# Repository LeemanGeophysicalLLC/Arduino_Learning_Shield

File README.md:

# Arduino_Learning_Shield
Shield to teach the basics of the Arduino platform.

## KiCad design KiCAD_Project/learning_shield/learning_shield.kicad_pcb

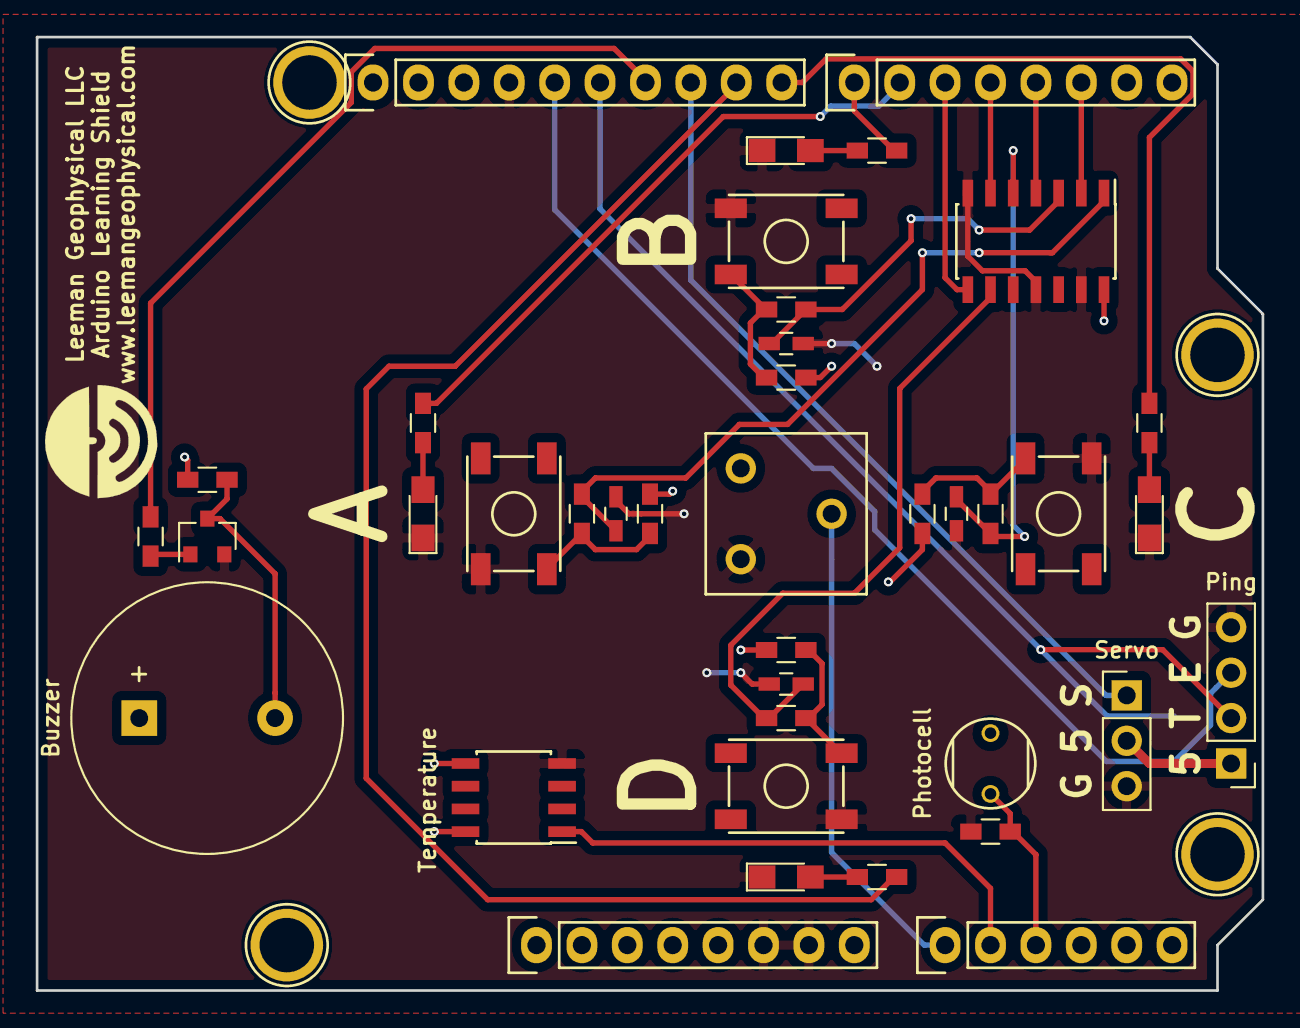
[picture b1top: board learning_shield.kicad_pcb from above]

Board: 2 copper layers, 68.6 x 53.3 mm, 43 parts (0 on the bottom side), 31 nets.

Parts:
BZ1: Buzzer; Buzzer_15x7.5RM7.6
C1, C2, C3, C4: C; C_0603_HandSoldering
D1, D2, D3, D4: LED A; LED_0805_HandSoldering
J1: Ping Sensor; Pin_Header_Straight_1x04_Pitch2.54mm
J2: Servo; Pin_Header_Straight_1x03_Pitch2.54mm
P1: Power; Socket_Strip_Arduino_1x08
P2: Analog; Socket_Strip_Arduino_1x06
P3: Digital; Socket_Strip_Arduino_1x10
P4: Digital; Socket_Strip_Arduino_1x08
P5, P6, P7, P8: CONN_01X01; Arduino_1pin
Q1: MMBT3904; SOT-23
R1, R2, R3, R4, R5, R6, R7, R8, R10: 10k; R_0603_HandSoldering
R9: R_PHOTO; photoresistor
R11, R12, R13, R14: 510; R_0603_HandSoldering
R15, R16: 1k; R_0603_HandSoldering
RV1: R_POT; ebay_potentiometer
SW1: Switch A; ebay_button
SW2: Switch B; ebay_button
SW3: Switch C; ebay_button
SW4: Switch D; ebay_button
U1: 74HC14; SOIC-14_3.9x8.7mm_Pitch1.27mm
U2: TMP36xS; SOIC-8_3.9x4.9mm_Pitch1.27mm

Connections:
+5V: BZ1.1, J1.1, J2.2, P1.5, R1.2, R2.2, R5.2, R6.2, R9.2, R16.2, RV1.1, U1.14, U2.5, U2.8
/2: P4.6, U1.2
/3(**): P4.5, U1.4
/4: P4.4, U1.6
/5(**): P4.3, U1.8
/6(**): P4.2, R11.2
/7: P4.1, R12.2
/8: P3.10, R13.2
/9(**): P3.9, R14.2
/10(**/SS): J2.1, P3.8
/11(**/MOSI): P3.7, R15.2
/12(MISO): J1.2, P3.6
/13(SCK): J1.3, P3.5
/A0: P2.1, RV1.2
/A1: P2.2, U2.1
/A2: P2.3, R9.1, R10.1
GND: C1.2, C2.2, C3.2, C4.2, D1.1, D2.1, D3.1, D4.1, J1.4, J2.3, P1.6, P1.7, P3.4, Q1.2, R10.2, RV1.3, SW1.1, SW2.1, SW3.1, SW4.1, U1.7, U1.11, U1.13, U2.4
unnamed: BZ1.2, Q1.3, R16.1
unnamed: C1.1, R3.2, U1.1
unnamed: C2.1, R4.2, U1.3
unnamed: C3.1, R7.2, U1.5
unnamed: C4.1, R8.2, U1.9
unnamed: D1.2, R11.1
unnamed: D2.2, R12.1
unnamed: D3.2, R13.1
unnamed: D4.2, R14.1
unnamed: Q1.1, R15.1
unnamed: R1.1, R3.1, SW1.2
unnamed: R2.1, R4.1, SW2.2
unnamed: R5.1, R7.1, SW3.2
unnamed: R6.1, R8.1, SW4.2

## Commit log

2020-01-01 Initial draft for Rev 1.0
2020-07-10 Update part numbers and population status.
2021-02-10 Add final BOM/files
